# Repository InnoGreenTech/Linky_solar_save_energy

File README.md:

# Linky_solar_save_energy
This is a controller of a hot water tank, it is able to read TIC linky and to adjust the power to absord the solar production.

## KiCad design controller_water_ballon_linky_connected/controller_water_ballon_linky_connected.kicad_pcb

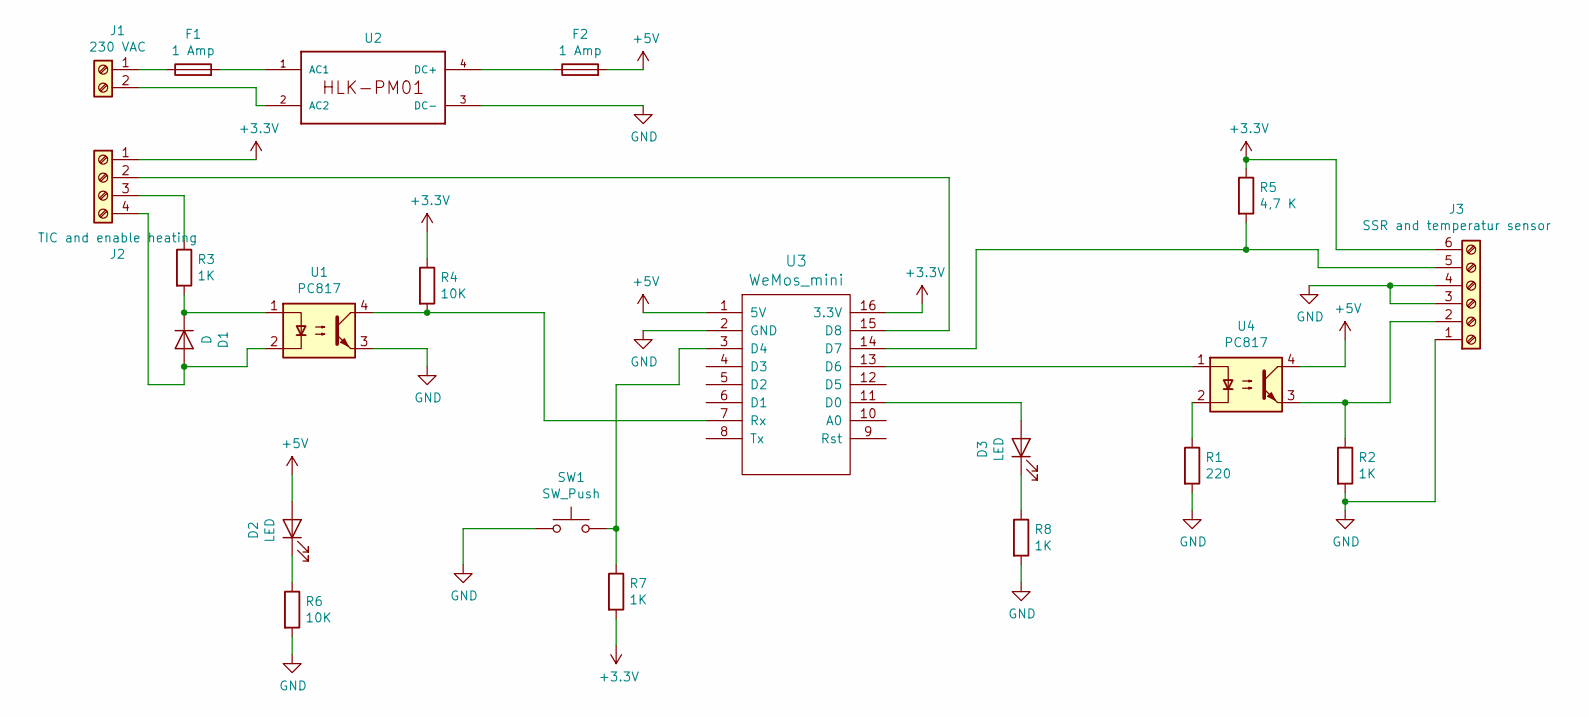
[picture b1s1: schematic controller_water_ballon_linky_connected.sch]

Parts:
D1: D; D_DO-15_P12.70mm_Horizontal
D2, D3: LED; LED_D3.0mm
F1, F2: 1 Amp; R_Axial_DIN0309_L9.0mm_D3.2mm_P15.24mm_Horizontal
J1: 230 VAC; TerminalBlock_bornier-2_P5.08mm
J2: TIC and enable heating; TerminalBlock_Phoenix_PT-1,5-4-3.5-H_1x04_P3.50mm_Horizontal
J3: SSR and temperatur sensor; TerminalBlock_Phoenix_PT-1,5-6-3.5-H_1x06_P3.50mm_Horizontal
R1: 220; R_Axial_DIN0309_L9.0mm_D3.2mm_P12.70mm_Horizontal
R2, R3, R7, R8: 1K; R_Axial_DIN0309_L9.0mm_D3.2mm_P12.70mm_Horizontal
R4, R6: 10K; R_Axial_DIN0309_L9.0mm_D3.2mm_P12.70mm_Horizontal
R5: 4,7 K; R_Axial_DIN0309_L9.0mm_D3.2mm_P12.70mm_Horizontal
SW1: SW_Push; SW_PUSH_6mm_H9.5mm
U1, U4: PC817; DIP-4_W7.62mm
U2: HLK-PM01
U3: WeMos_mini; D1_mini_board

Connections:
+3V3: J2.1, J3.6, R4.1, R5.1, R7.2, U3.16 (3.3V)
+5V: D2.2 (A), F2.2, U3.1 (5V), U4.4
GND: J3.1, J3.3, J3.4, R1.2, R2.2, R6.2, R8.2, SW1.1, U1.3, U2.3 (DC-), U3.2 (GND)
unnamed: D1.1 (K), R3.2, U1.1
unnamed: D1.2 (A), J2.4, U1.2
unnamed: D2.1 (K), R6.1
unnamed: D3.1 (K), R8.1
unnamed: D3.2 (A), U3.11 (D0)
unnamed: F1.1, J1.1
unnamed: F1.2, U2.1 (AC1)
unnamed: F2.1, U2.4 (DC+)
unnamed: J1.2, U2.2 (AC2)
unnamed: J2.2, U3.15 (D8)
unnamed: J2.3, R3.1
unnamed: J3.2, R2.1, U4.3
unnamed: J3.5, R5.2, U3.14 (D7)
unnamed: R1.1, U4.2
unnamed: R4.2, U1.4, U3.7 (Rx)
unnamed: R7.1, SW1.2, U3.3 (D4)
unnamed: U3.13 (D6), U4.1

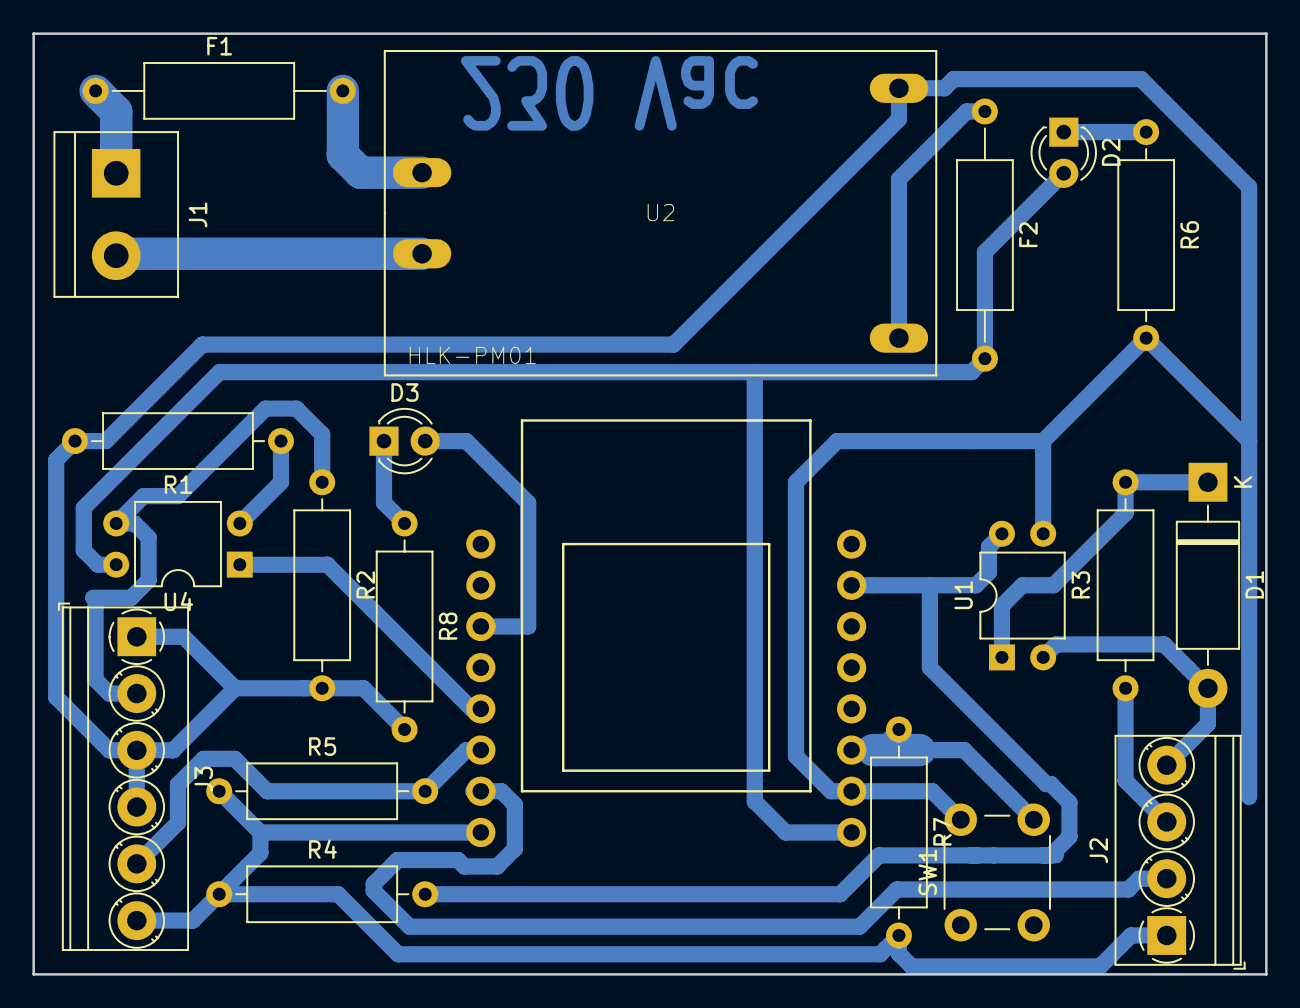
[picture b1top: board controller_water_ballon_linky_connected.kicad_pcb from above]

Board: 2 copper layers, 76.0 x 58.0 mm, 21 parts (1 on the bottom side), 20 nets.

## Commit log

2021-01-17 improve the heating beavior
2021-04-01 adjust recover solar energy
2021-04-23 diseable PID and add intensity control to adjust power recovery
2021-04-24 New process regulation*
2022-08-19 modification avec timer 1
